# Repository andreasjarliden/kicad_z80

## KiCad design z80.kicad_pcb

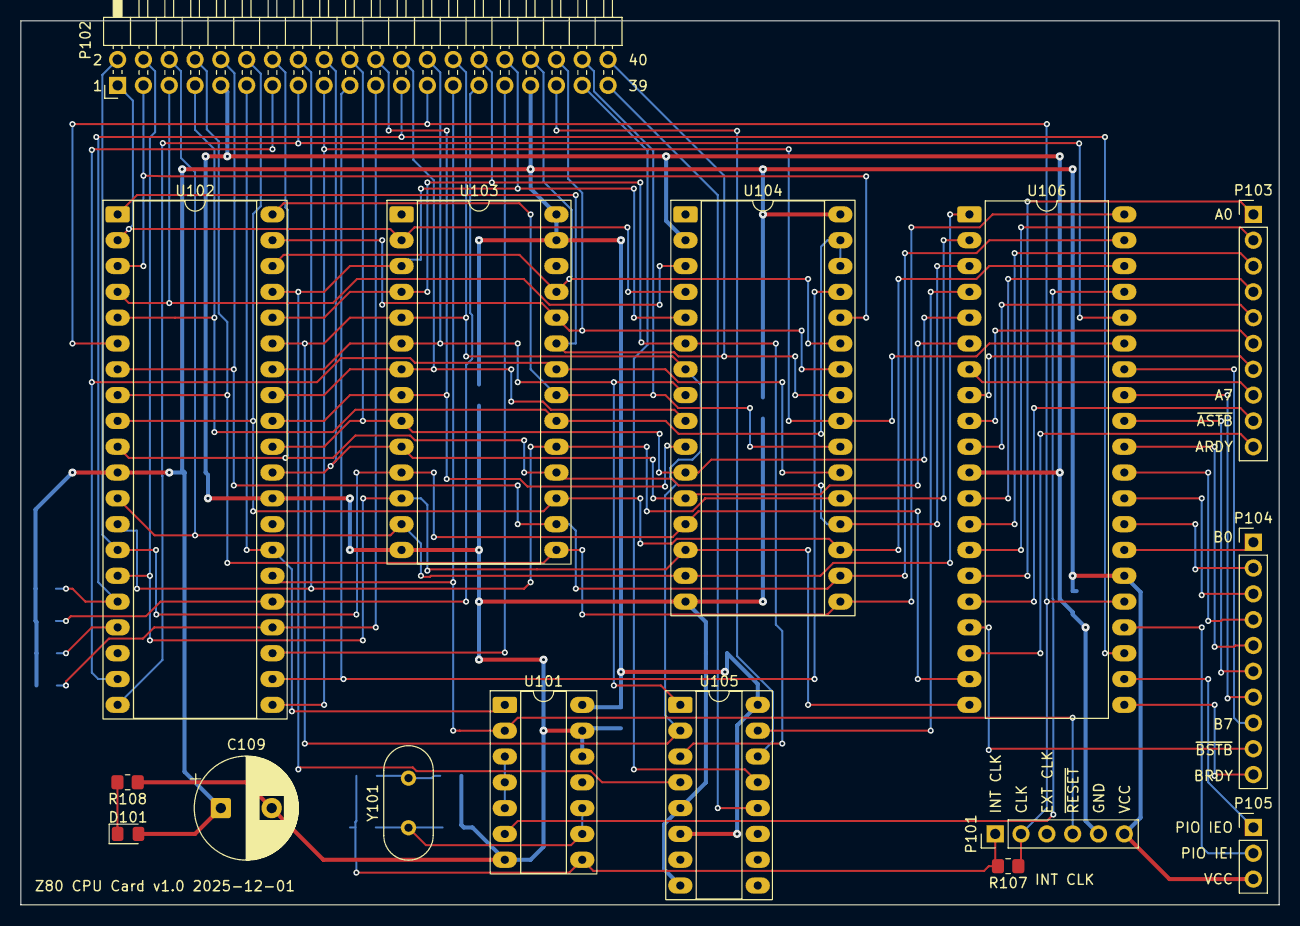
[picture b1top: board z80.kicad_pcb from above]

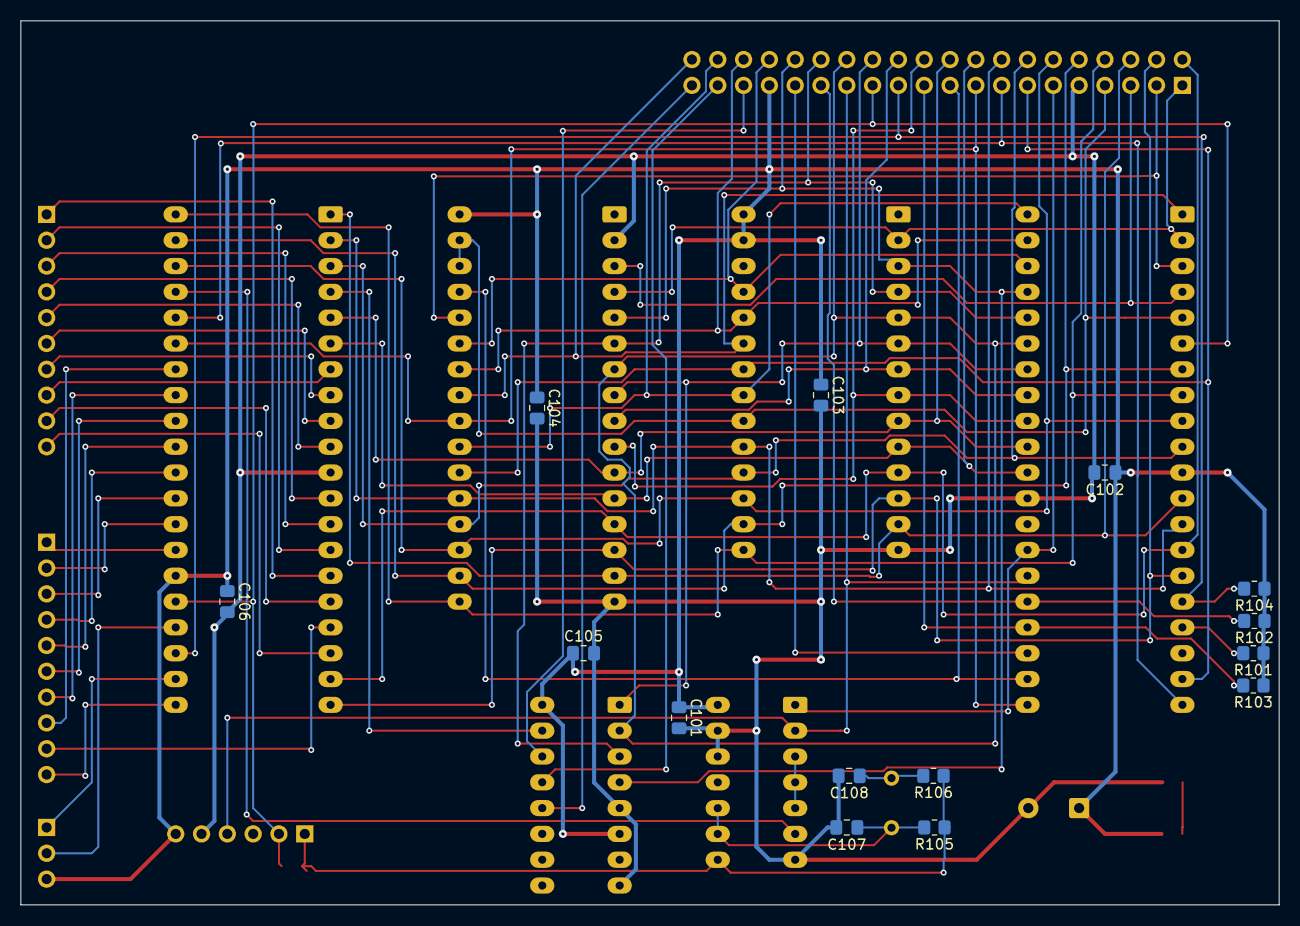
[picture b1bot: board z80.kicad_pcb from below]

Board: 2 copper layers, 123.8 x 87.0 mm, 30 parts (14 on the bottom side), 70 nets.

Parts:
C101, C102, C103, C104, C105, C106: 0.1u; C_0805_2012Metric_Pad1.18x1.45mm_HandSolder
C107, C108: 22pF; C_0805_2012Metric_Pad1.18x1.45mm_HandSolder
C109: 10u; CP_Radial_D10.0mm_P5.00mm
D101: LED; LED_0805_2012Metric_Pad1.15x1.40mm_HandSolder
P101: CONN_01X04; PinHeader_1x06_P2.54mm_Vertical
P102: CONN_02X20; PinHeader_2x20_P2.54mm_Horizontal
P103, P104: CONN_01X10; PinHeader_1x10_P2.54mm_Vertical
P105: PinHeader_1x03_P2.54mm_Vertical
R101, R102, R103, R104: 10k; R_0805_2012Metric_Pad1.20x1.40mm_HandSolder
R105: 1M; R_0805_2012Metric_Pad1.20x1.40mm_HandSolder
R106: 2k; R_0805_2012Metric_Pad1.20x1.40mm_HandSolder
R107: 0; R_0805_2012Metric_Pad1.20x1.40mm_HandSolder
R108: 470; R_0805_2012Metric_Pad1.20x1.40mm_HandSolder
U101: 7400; DIP-14_W7.62mm_Socket_LongPads
U102: Z8400; DIP-40_W15.24mm_Socket_LongPads
U103: AT28C64B; DIP-28_W15.24mm_Socket_LongPads
U104: AS6C1008; DIP-32_W15.24mm_Socket_LongPads
U105: 74LS138; DIP-16_W7.62mm_Socket_LongPads
U106: Z8420; DIP-40_W15.24mm_LongPads
Y101: 4MHz; Crystal_HC49-4H_Vertical

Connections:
/CLK_INT: P101.1, R105.1, R106.1, R107.2, U101.8
/PIO_A0: P103.1, U106.15 (A0)
/PIO_A1: P103.2, U106.14 (A1)
/PIO_A2: P103.3, U106.13 (A2)
/PIO_A3: P103.4, U106.12 (A3)
/PIO_A4: P103.5, U106.10 (A4)
/PIO_A5: P103.6, U106.9 (A5)
/PIO_A6: P103.7, U106.8 (A6)
/PIO_A7: P103.8, U106.7 (A7)
/PIO_ARDY: P103.10, U106.18 (ARDY)
/PIO_B0: P104.1, U106.27 (B0)
/PIO_B1: P104.2, U106.28 (B1)
/PIO_B2: P104.3, U106.29 (B2)
/PIO_B3: P104.4, U106.30 (B3)
/PIO_B4: P104.5, U106.31 (B4)
/PIO_B5: P104.6, U106.32 (B5)
/PIO_B6: P104.7, U106.33 (B6)
/PIO_B7: P104.8, U106.34 (B7)
/PIO_BRDY: P104.10, U106.21 (BRDY)
/PIO_IEI: P105.2, U106.24 (IEI)
/PIO_IEO: P105.1, U106.22 (IEO)
/~PIO_ASTB: P103.9, U106.16 (~ASTB)
/~PIO_BSTB: P104.9, U106.17 (~BSTB)
/~PIO_CE: U105.15 (O0), U106.4 (~CE)
/~PIO_M1: U101.6, U106.37 (~M1)
A0: P102.18, U102.30 (A0), U103.10 (A0), U104.12 (A0), U106.6 (B/~A)
A1: P102.20, U102.31 (A1), U103.9 (A1), U104.11 (A1), U106.5 (C/~D)
A2: P102.22, U102.32 (A2), U103.8 (A2), U104.10 (A2)
A3: P102.24, U102.33 (A3), U103.7 (A3), U104.9 (A3)
A4: P102.26, U102.34 (A4), U103.6 (A4), U104.8 (A4), U105.1 (A0)
A5: P102.28, U102.35 (A5), U103.5 (A5), U104.7 (A5), U105.2 (A1)
A6: P102.30, U102.36 (A6), U103.4 (A6), U104.6 (A6), U105.3 (A2)
A7: P102.32, U102.37 (A7), U103.3 (A7), U104.5 (A7), U105.4 (E1)
A8: P102.34, U102.38 (A8), U103.25 (A8), U104.27 (A8)
A9: P102.36, U102.39 (A9), U103.24 (A9), U104.26 (A9)
A10: P102.38, U102.40 (A10), U103.21 (A10), U104.23 (A10)
A11: P102.40, U102.1 (A11), U103.23 (A11), U104.25 (A11)
A12: P102.1, U102.2 (A12), U103.2 (A12), U104.4 (A12)
A13: P102.3, U102.3 (A13), U104.28 (A13)
A14: P102.5, U102.4 (A14), U104.3 (A14)
A15: P102.7, U102.5 (A15), U103.20 (~CS), U104.30 (CE2), U104.31 (A15)
CLK: P101.2, P102.25, R107.1, U102.6 (CLK), U106.25 (CLK)
D0: P102.2, U102.14 (D0), U103.11 (D0), U104.13 (D0), U106.19 (D0)
D1: P102.4, U102.15 (D1), U103.12 (D1), U104.14 (D1), U106.20 (D1)
D2: P102.6, U102.12 (D2), U103.13 (D2), U104.15 (D2), U106.1 (D2)
D3: P102.8, U102.8 (D3), U103.15 (D3), U104.17 (D3), U106.40 (D3)
D4: P102.10, U102.7 (D4), U103.16 (D4), U104.18 (D4), U106.39 (D4)
D5: P102.12, U102.9 (D5), U103.17 (D5), U104.19 (D5), U106.38 (D5)
D6: P102.14, U102.10 (D6), U103.18 (D6), U104.20 (D6), U106.3 (D6)
D7: P102.16, U102.13 (D7), U103.19 (D7), U104.21 (D7), U106.2 (D7)
GND: C101.2, C102.2, C103.2, C104.2, C105.2, C106.2, C107.2, C108.2, C109.2, P101.5, P102.9, R108.1, U101.7 (GND), U101.12, U101.13, U102.29 (GND), U103.14 (GND), U104.2 (A16), U104.16 (GND), U105.5 (E2), U105.8 (GND), U106.11 (GND)
unnamed: C107.1, R105.2, U101.9, U101.10, Y101.1
unnamed: C108.1, R106.2, Y101.2
unnamed: D101.1 (K), R108.2
unnamed: U101.3, U101.4, U101.5
VCC: C101.1, C102.1, C103.1, C104.1, C105.1, C106.1, C109.1, D101.2 (A), P101.6, P102.33, P105.3, R101.1, R102.1, R103.1, R104.1, U101.14 (VCC), U102.11 (+5V), U103.27 (~WE), U103.28 (VCC), U104.32 (VCC), U105.6 (E3), U105.16 (VCC), U106.26 (VCC)
~BUSACK: P102.31, U102.23 (~BUSACK)
~BUSREQ: P102.29, R102.2, U102.25 (~BUSREQ)
~CE_3: P102.39, U105.12 (O3)
~CTC_CE: P102.35, U105.14 (O1)
~INT: P102.23, R104.2, U102.16 (~INT), U106.23 (~INT)
~IORQ: P102.15, U102.20 (~IORQ), U106.36 (~IORQ)
~M1: P102.11, U101.1, U102.27 (~M1)
~MREQ: P102.13, U102.19 (~MREQ), U103.22 (~OE), U104.22 (~CE1)
~NMI: R101.2, U102.17 (~NMI)
~RD: P102.17, U102.21 (~RD), U104.24 (~OE), U106.35 (~RD)
~RESET: P101.4, P102.27, U101.2, U102.26 (~RESET)
~SIO_CE: P102.37, U105.13 (O2)
~WAIT: P102.21, R103.2, U102.24 (~WAIT)
~WR: P102.19, U102.22 (~WR), U104.29 (~WR)

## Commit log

2015-03-14 Connect ~RESET to the PIO
2015-03-14 Add PIO port A connector and 40 pin bus connector
2015-03-19 Commit before removing tracks
2015-03-21 More routing
2015-03-22 More routing. Adding decoupling and ~INT pull-up
2015-12-19 Add crystal clock circuit
2017-03-08 Begun adding SIO
2025-10-03 Unknown timer changes
2025-10-07 Added z80-cache.lib file
2025-10-07 Converted to KiCad 9
2025-10-21 WIP solving ERC issues
2025-10-23 Fixed all schematic ERC errors and warnings
2025-11-10 Added .gitignore file
2025-11-10 Started on pcb. WIP
2025-11-13 Begun pcb routing. WIP
2025-11-18 More PCB routing. All ICs on CPU board now routed.
2025-11-27 Continued layout of timer/sio board
2025-11-29 PCB routing almost complete
2025-11-30 Removed serial board which has now been moved to its own project.
2025-12-04 Completed and ordered.
